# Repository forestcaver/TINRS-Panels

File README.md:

# TINRS-Panels
Tuesday Panel - verified and built

Wobbler Panel - verified and built

Rectangular Thing Panel - verified and built

Hedge Trimmer pcb and panel (Edgecutter with thonkiconn jacks and LP4OA1PBCTG led switch) - verified and built (one hole is not drilled - oops ! I'll update the gerber soon !)

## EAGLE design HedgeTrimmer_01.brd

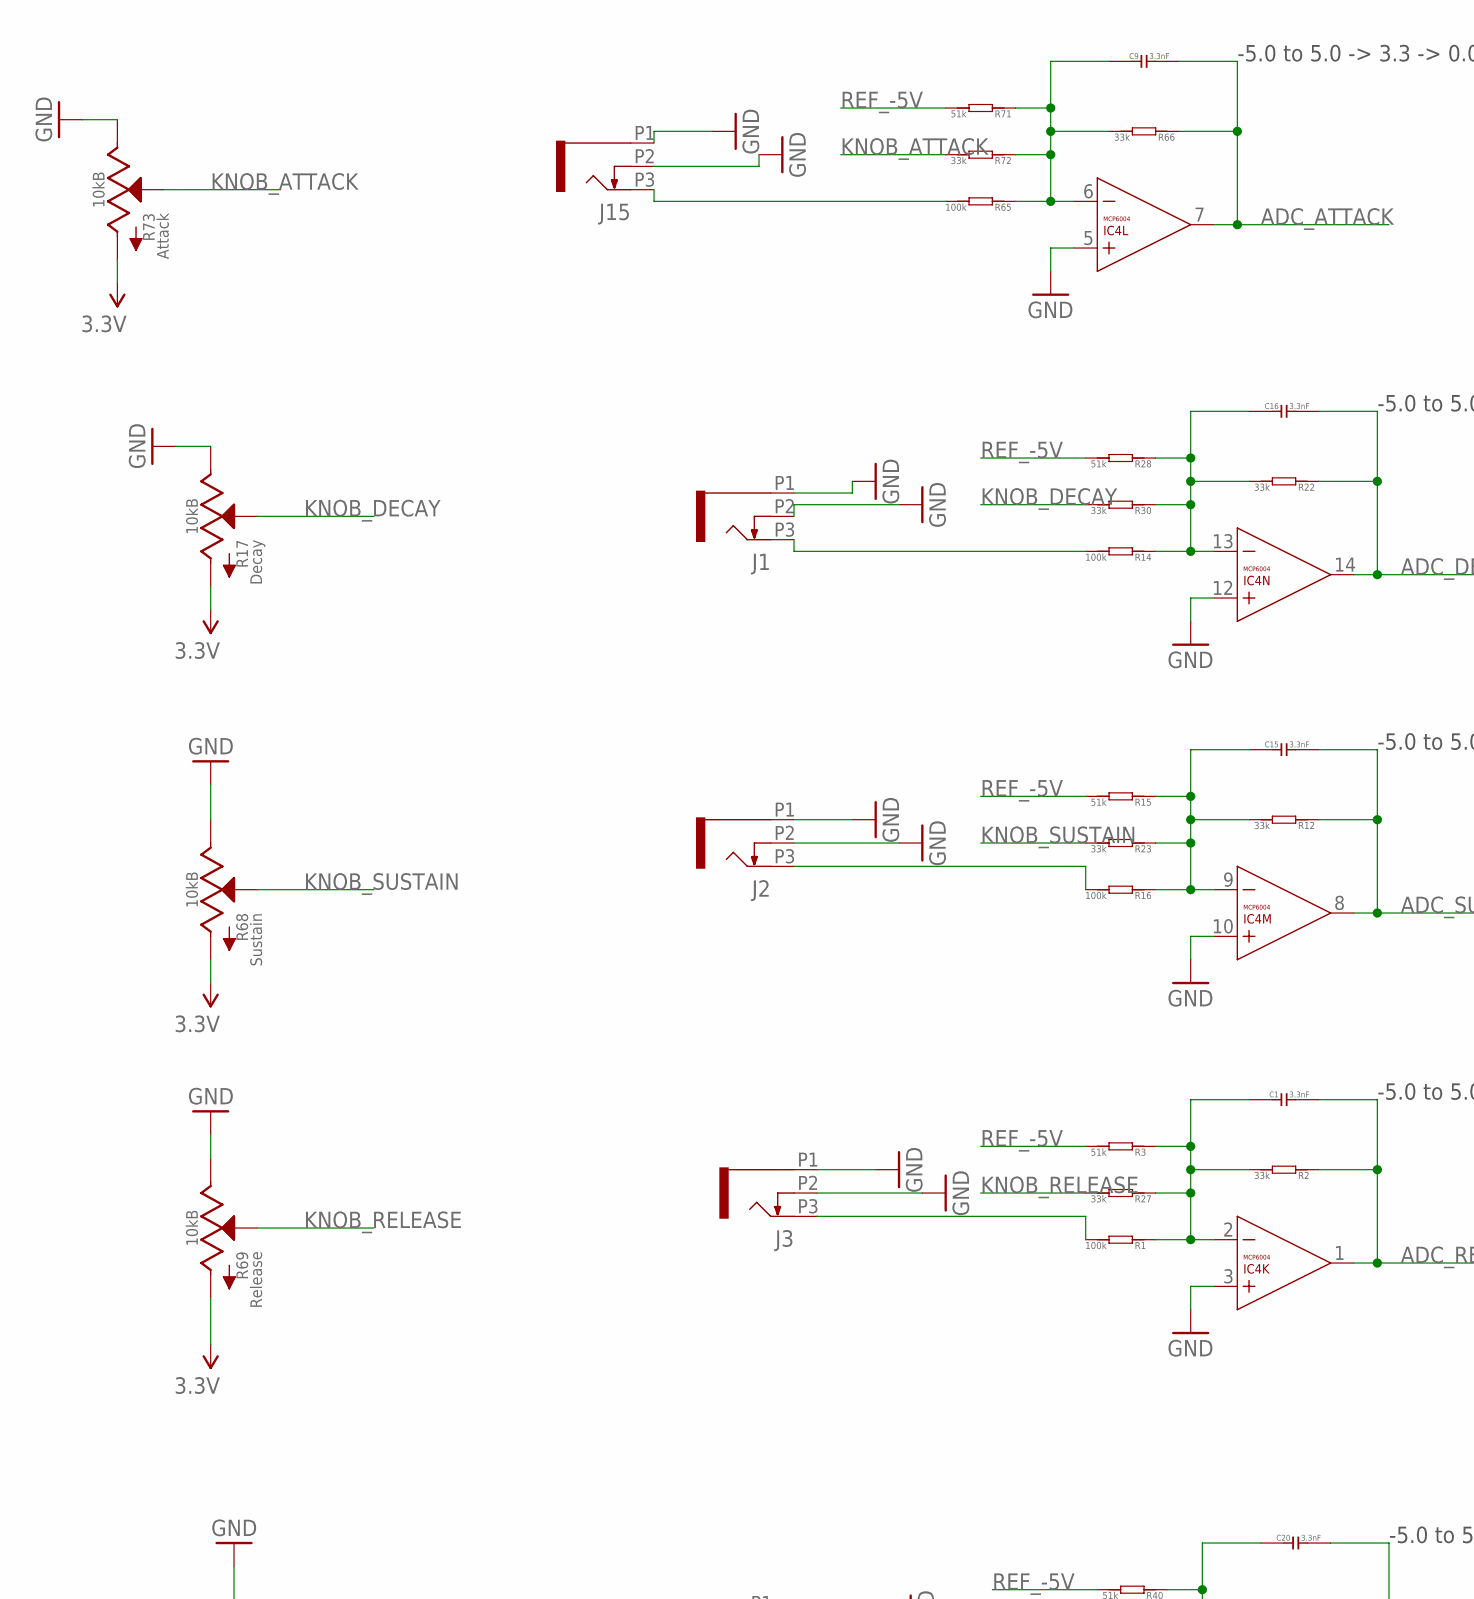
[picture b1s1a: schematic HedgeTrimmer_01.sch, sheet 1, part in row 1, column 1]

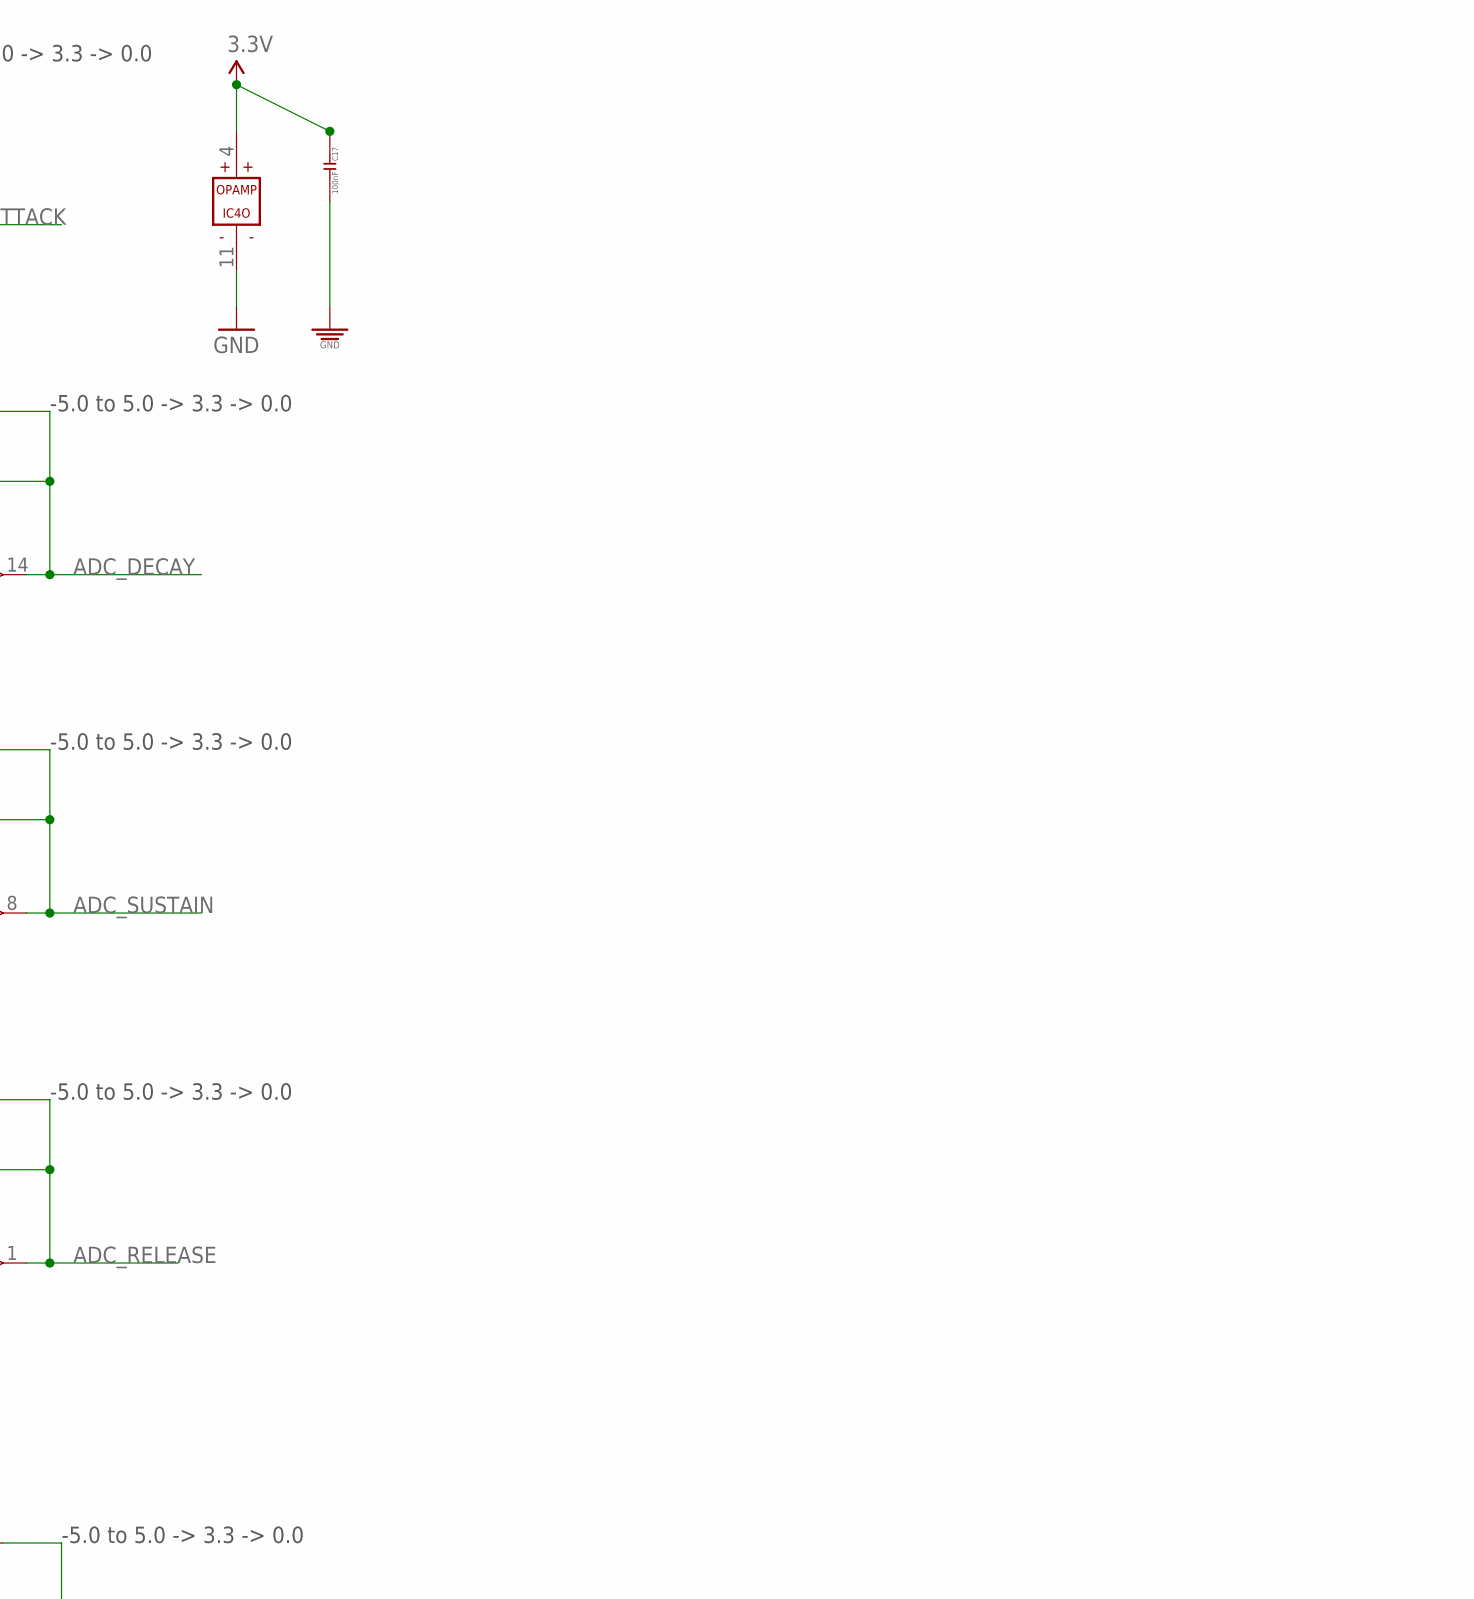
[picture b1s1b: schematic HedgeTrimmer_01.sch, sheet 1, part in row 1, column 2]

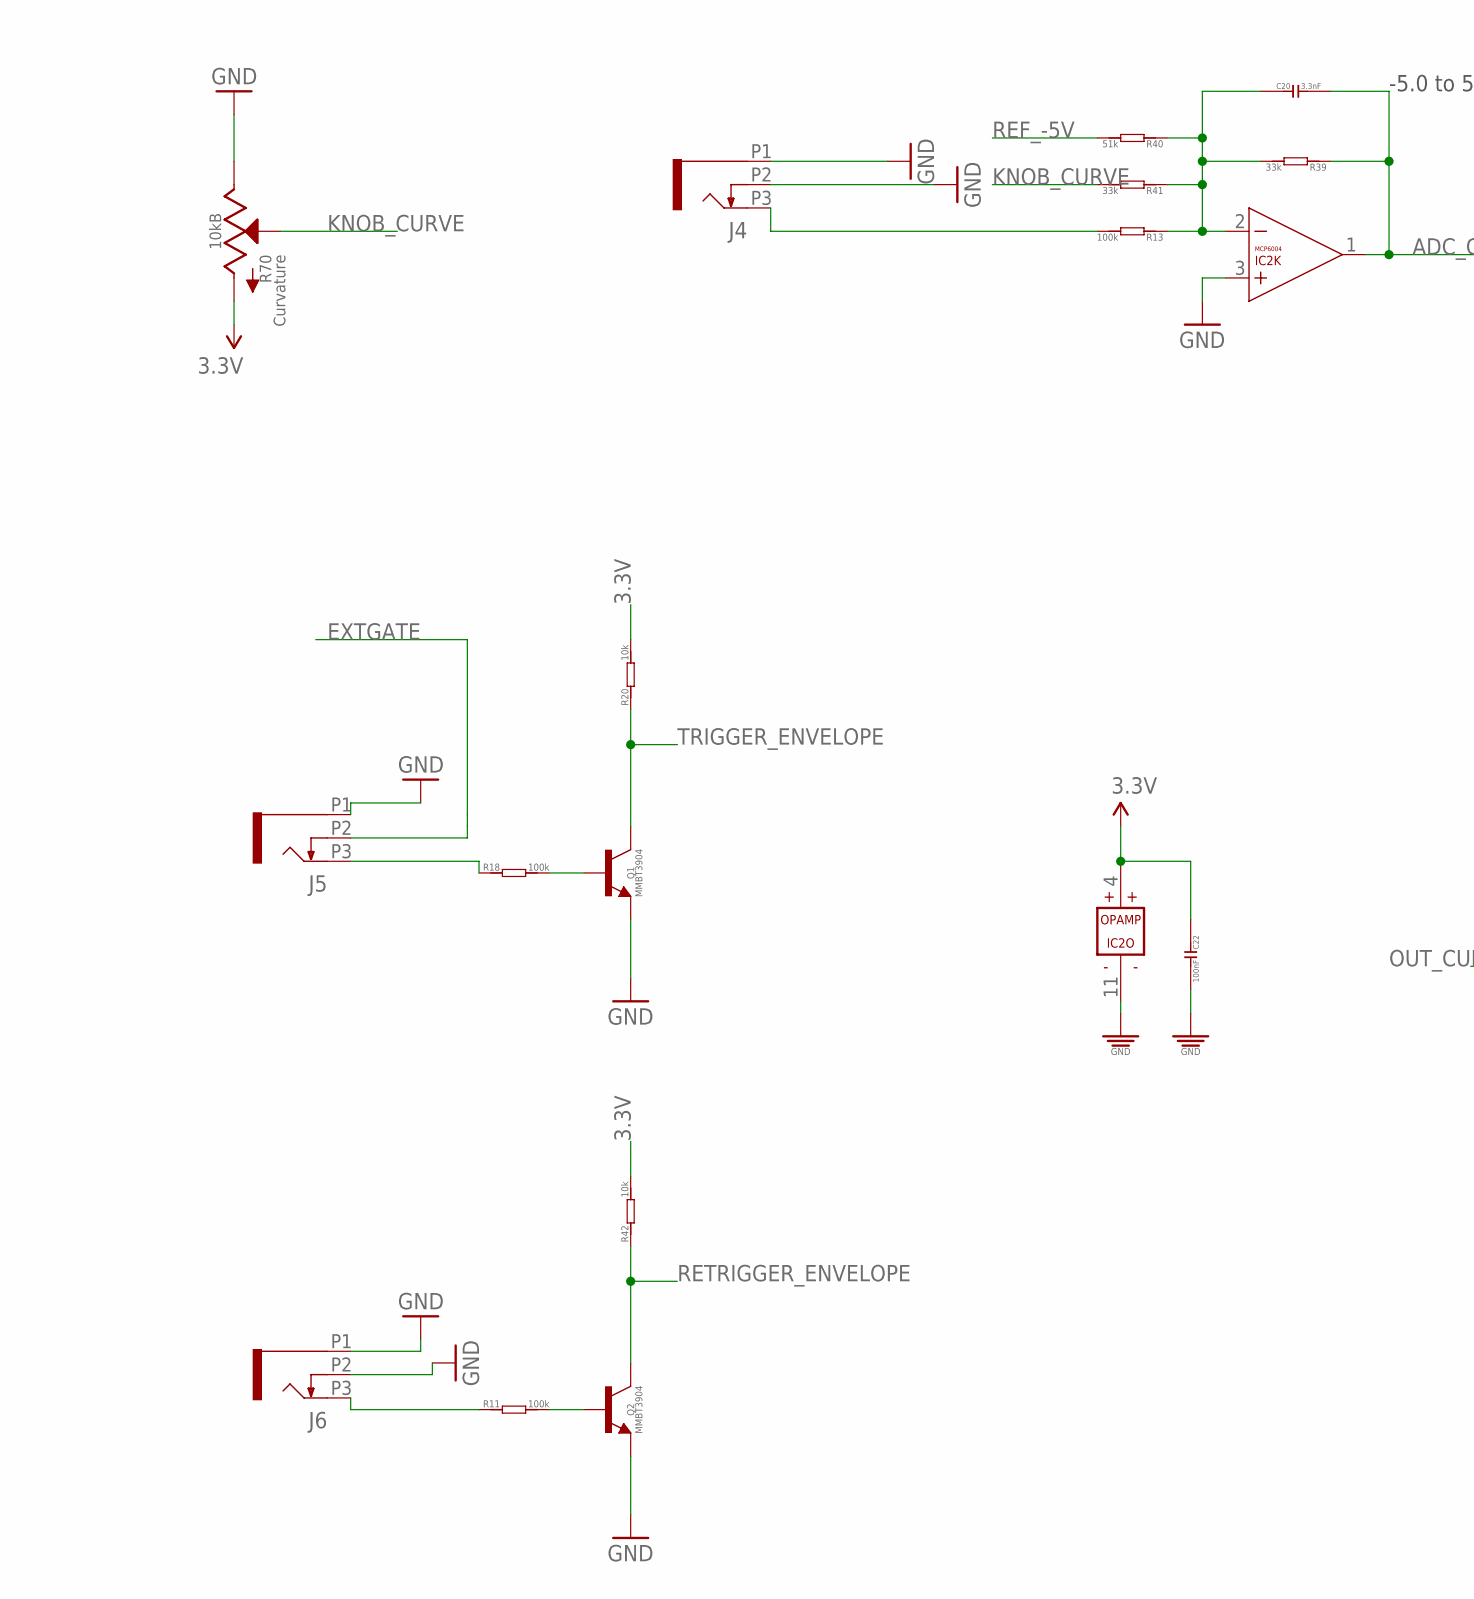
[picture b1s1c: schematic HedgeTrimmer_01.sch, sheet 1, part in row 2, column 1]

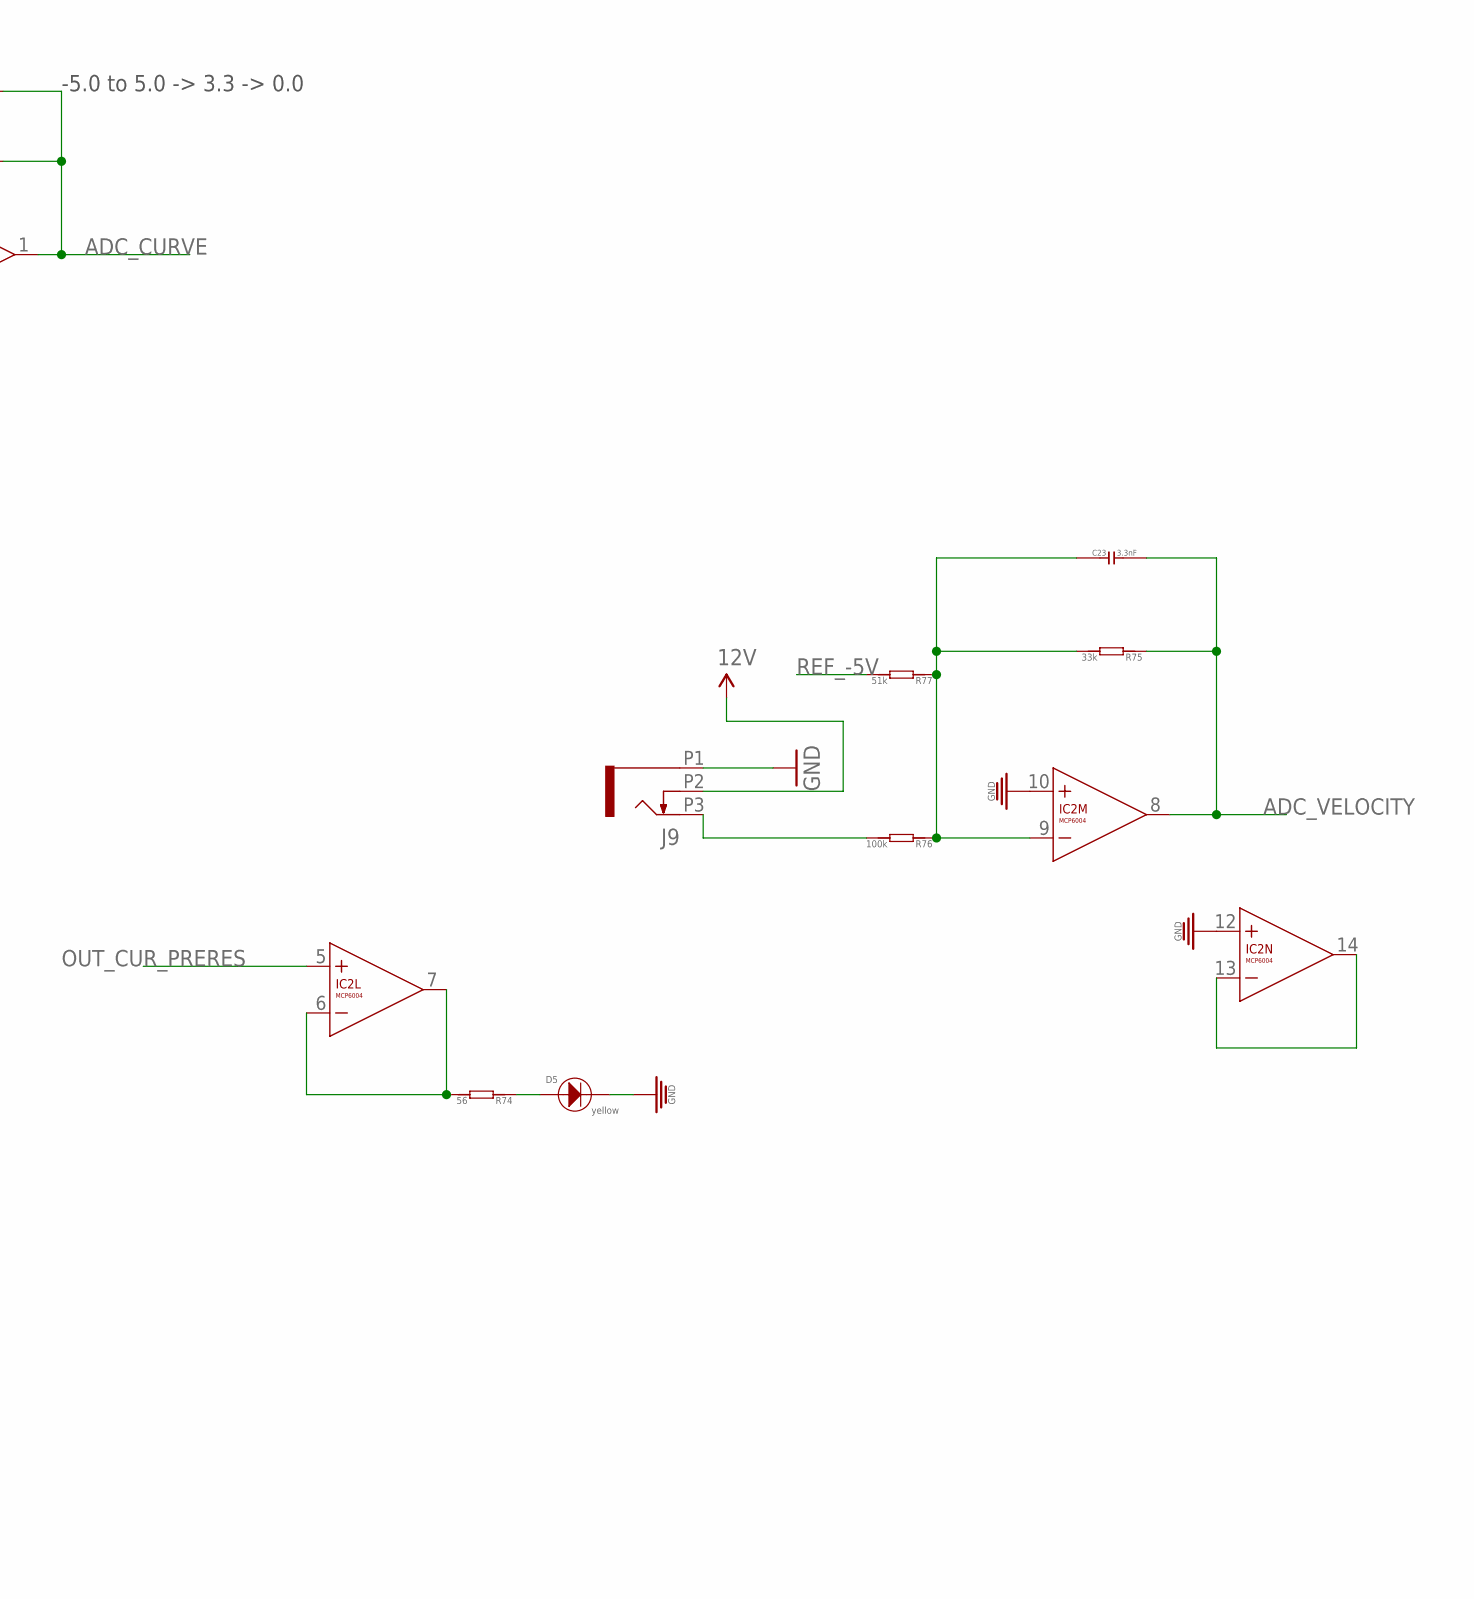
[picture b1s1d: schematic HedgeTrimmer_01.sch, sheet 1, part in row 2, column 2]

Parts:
C1, C9, C15, C16, C20, C23: 3.3nF; C0603
C17, C22: 100nF; C0603; MPN MC0603F104Z160CT
D5: yellow; 3MMLED
IC2, IC4: MCP6004; SO14; MPN MCP6004-I/SL.
J1, J2, J3, J4, J5, J6, J9, J15: PJ301_THONKICONN8; WQP_PJ_301M8
Q1, Q2: MMBT3904; SOT23-BEC; MPN PMBT3904,215
R1, R11, R13, R14, R16, R18, R65, R76: 100k; R0603
R2, R12, R22, R23, R27, R30, R39, R41, R66, R72, R75: 33k; R0603
R3, R15, R28, R40, R71, R77: 51k; R0603
R17, R68, R69, R70, R73: 10kB; OG-POTS_ALPS_POT_VERTICAL
R20, R42: 10k; R0603
R74: 56; R0603

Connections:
3.3V: C17.1, C22.1, IC2.4 (V+), IC4.4 (V+), R17.P$3 (A), R20.2, R42.2, R68.P$3 (A), R69.P$3 (A), R70.P$3 (A), R73.P$3 (A); also elsewhere on the board
12V: J9.P2 (2); also elsewhere on the board
ADC_ATTACK: C9.2, IC4.7 (OUT), R66.1; also elsewhere on the board
ADC_CURVE: C20.2, IC2.1 (OUT), R39.1; also elsewhere on the board
ADC_DECAY: C16.2, IC4.14 (OUT), R22.1; also elsewhere on the board
ADC_RELEASE: C1.2, IC4.1 (OUT), R2.1; also elsewhere on the board
ADC_SUSTAIN: C15.2, IC4.8 (OUT), R12.1; also elsewhere on the board
ADC_VELOCITY: C23.2, IC2.8 (OUT), R75.1; also elsewhere on the board
EXTGATE: J5.P2 (2); also elsewhere on the board
GND: C17.2, C22.2, D5.-, IC2.3 (+IN), IC2.10 (+IN), IC2.11 (V-), IC2.12 (+IN), IC4.3 (+IN), IC4.5 (+IN), IC4.10 (+IN), IC4.11 (V-), IC4.12 (+IN), J1.P1 (1), J1.P2 (2), J2.P1 (1), J2.P2 (2), J3.P1 (1), J3.P2 (2), J4.P1 (1), J4.P2 (2), J5.P1 (1), J6.P1 (1), J6.P2 (2), J9.P1 (1), J15.P1 (1), J15.P2 (2), Q1.E, Q2.E, R17.P$1 (E), R68.P$1 (E), R69.P$1 (E), R70.P$1 (E), R73.P$1 (E); also elsewhere on the board
KNOB_ATTACK: R72.2, R73.P$2 (S)
KNOB_CURVE: R41.2, R70.P$2 (S)
KNOB_DECAY: R17.P$2 (S), R30.2
KNOB_RELEASE: R27.2, R69.P$2 (S)
KNOB_SUSTAIN: R23.2, R68.P$2 (S)
unnamed: J15.P3 (3), R65.2
unnamed: J2.P3 (3), R16.2
unnamed: C15.1, IC4.9 (-IN), R12.2, R15.1, R16.1, R23.1
unnamed: J3.P3 (3), R1.2
unnamed: C1.1, IC4.2 (-IN), R1.1, R2.2, R3.1, R27.1
unnamed: J1.P3 (3), R14.2
unnamed: J4.P3 (3), R13.2
unnamed: Q1.B, R18.2
unnamed: J5.P3 (3), R18.1
unnamed: IC2.6 (-IN), IC2.7 (OUT), R74.2
unnamed: J6.P3 (3), R11.1
unnamed: C9.1, IC4.6 (-IN), R65.1, R66.2, R71.1, R72.1
unnamed: IC2.13 (-IN), IC2.14 (OUT)
unnamed: J9.P3 (3), R76.2
unnamed: C16.1, IC4.13 (-IN), R14.1, R22.2, R28.1, R30.1
unnamed: Q2.B, R11.2
unnamed: C20.1, IC2.2 (-IN), R13.1, R39.2, R40.1, R41.1
unnamed: C23.1, IC2.9 (-IN), R75.2, R76.1, R77.1
unnamed: D5.+, R74.1
OUT_CUR_PRERES: IC2.5 (+IN); also elsewhere on the board
REF_-5V: R3.2, R15.2, R28.2, R40.2, R71.2, R77.2; also elsewhere on the board
RETRIGGER_ENVELOPE: Q2.C, R42.1; also elsewhere on the board
TRIGGER_ENVELOPE: Q1.C, R20.1; also elsewhere on the board

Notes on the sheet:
-5.0 to 5.0 -> 3.3 -> 0.0

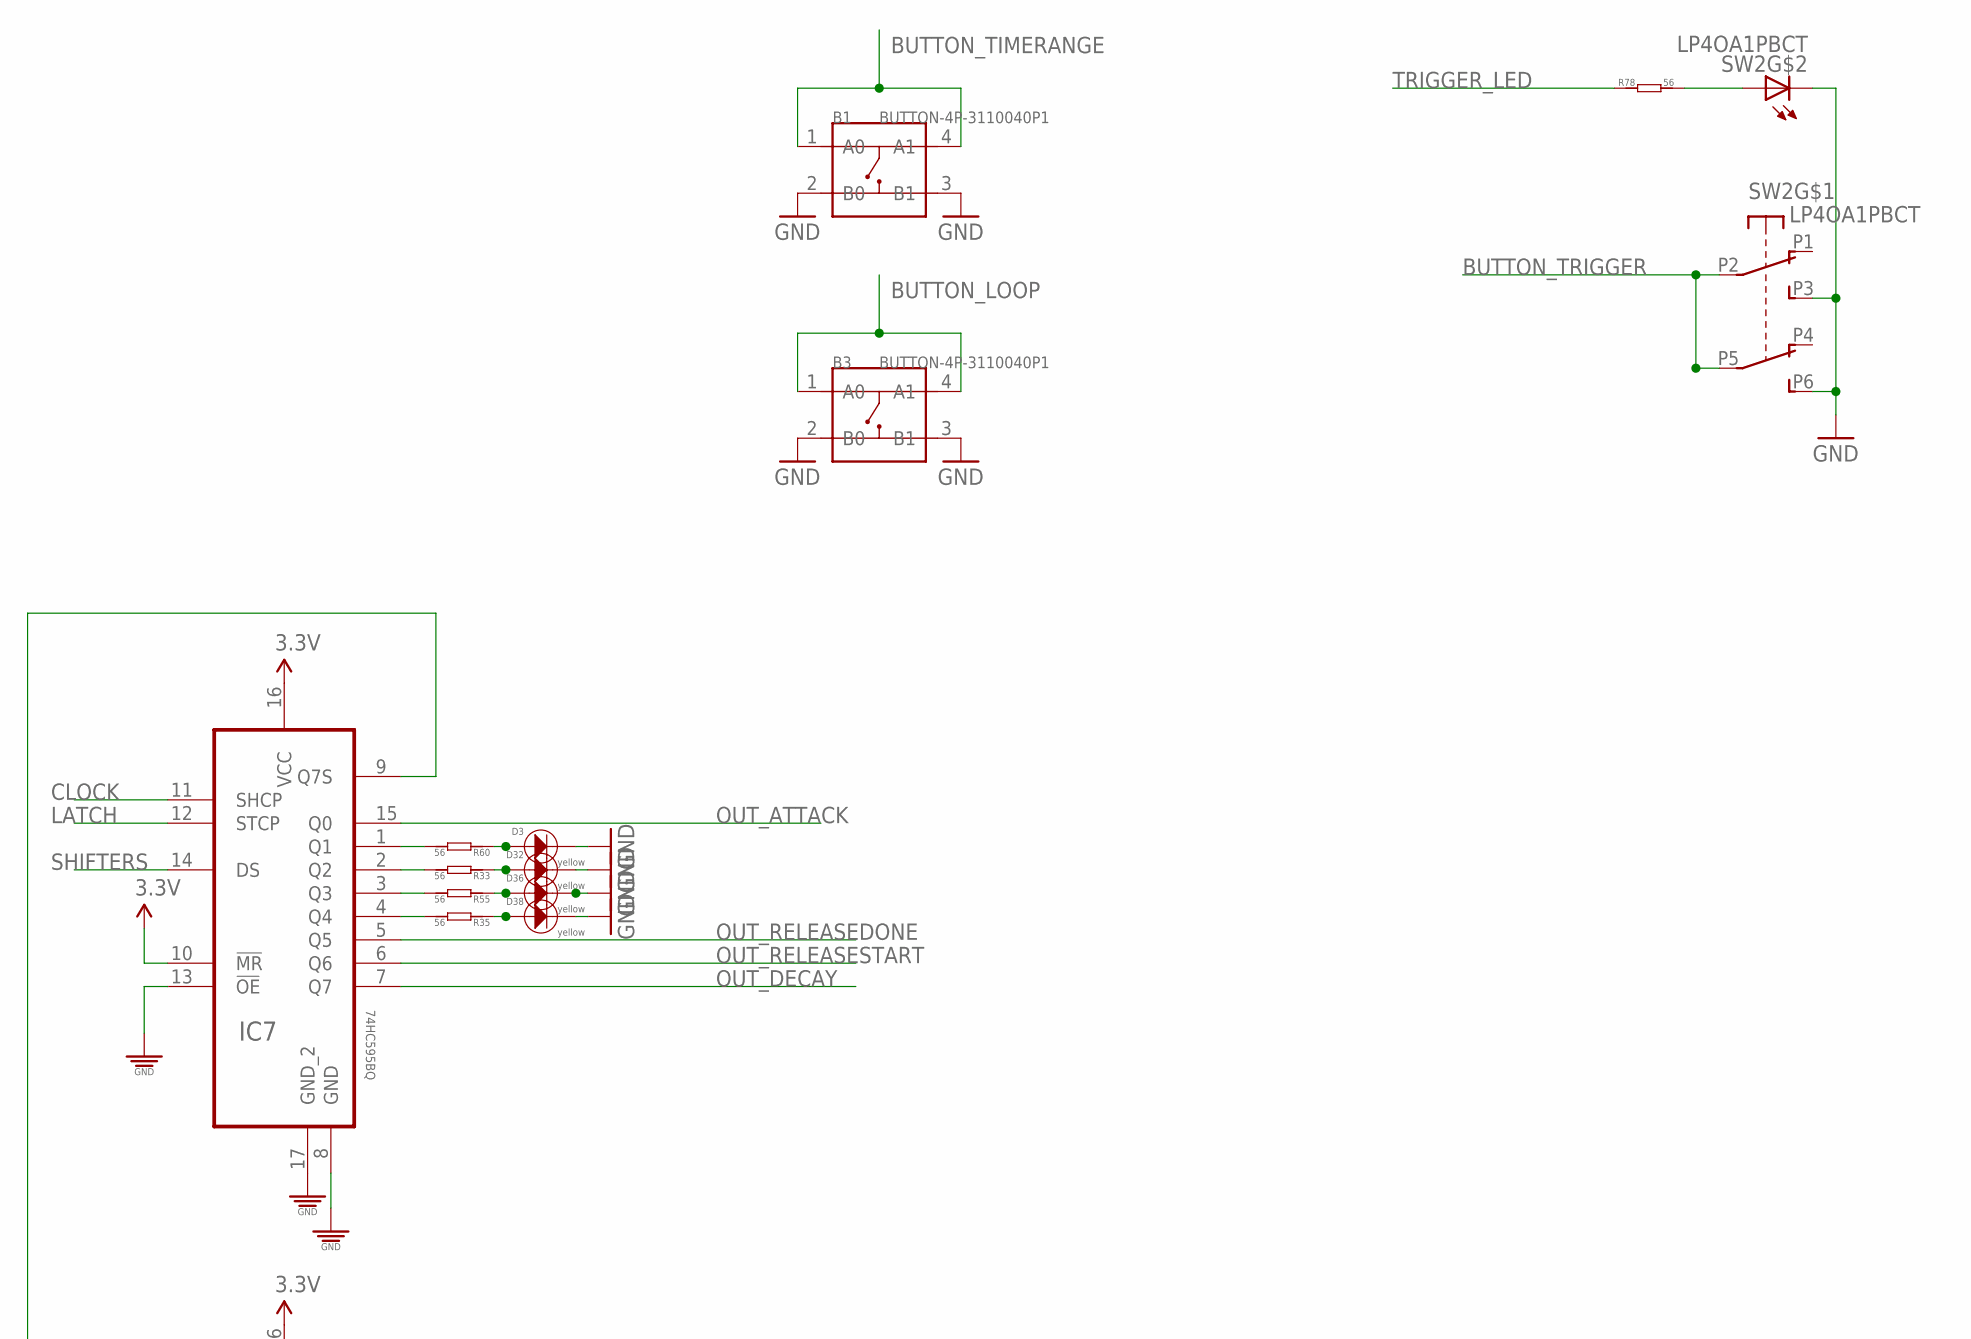
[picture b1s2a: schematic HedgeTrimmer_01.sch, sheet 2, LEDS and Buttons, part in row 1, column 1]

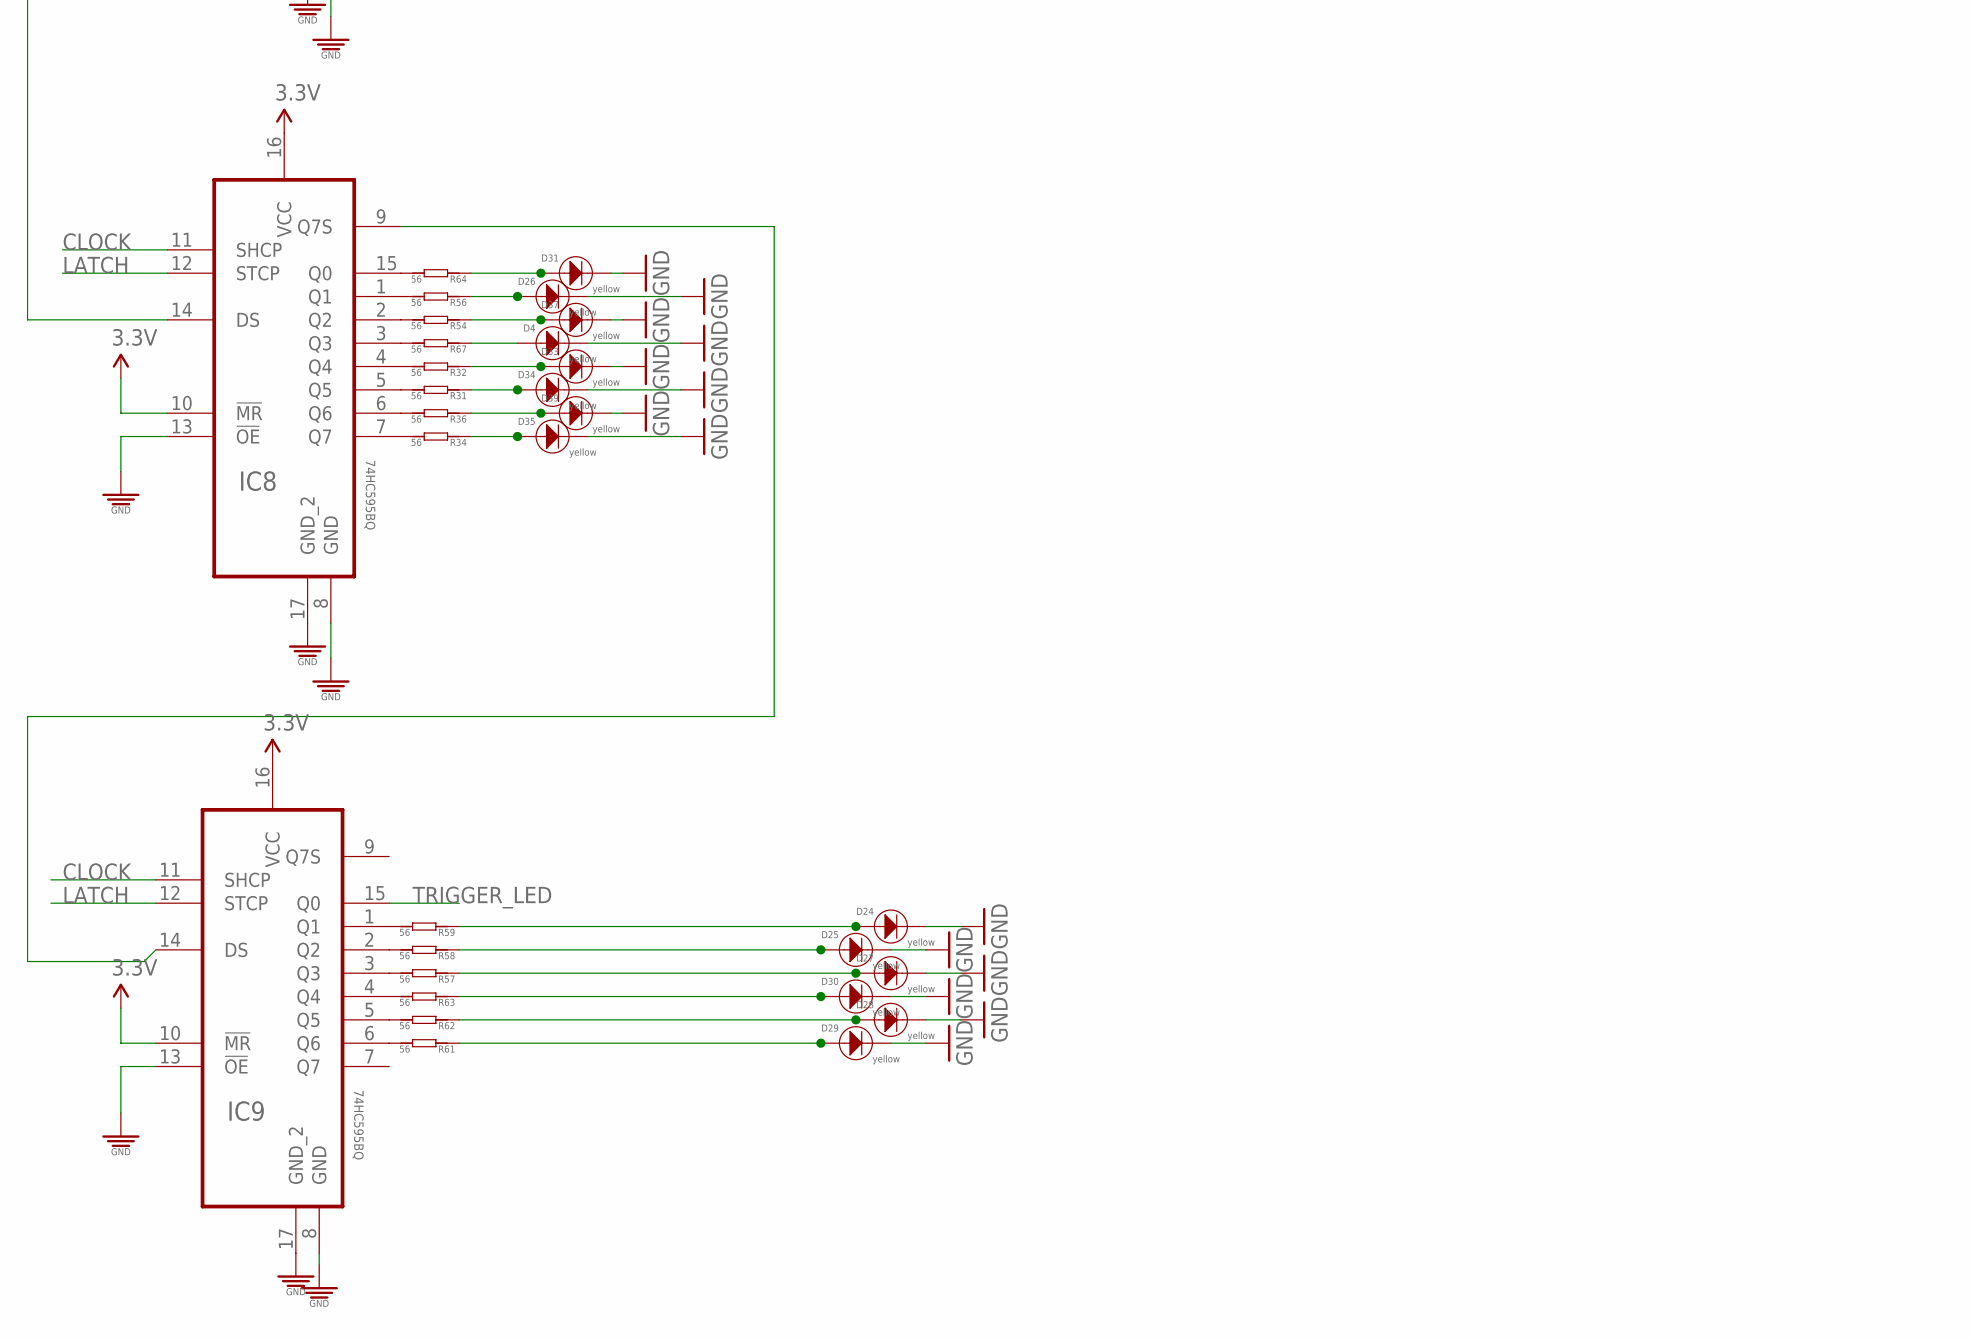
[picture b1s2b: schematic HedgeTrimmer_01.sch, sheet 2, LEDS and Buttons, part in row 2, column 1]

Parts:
B1, B3: BUTTON-4P-3110040P1; 4P-6.0X6.0X5.0H
D3, D4, D24, D25, D26, D27, D28, D29, D30, D31, D32, D33, D34, D35, D36, D37, D38, D39: yellow; 3MMLED
IC7, IC8, IC9: 74HC595BQ; QFN50P250X350X100-17N
R31, R32, R33, R34, R35, R36, R54, R55, R56, R57, R58, R59, R60, R61, R62, R63, R64, R67, R78: 56; R0603
SW2: LP4OA1PBCT

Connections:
3.3V: IC7.10 (!MR), IC7.16 (VCC), IC8.10 (!MR), IC8.16 (VCC), IC9.10 (!MR), IC9.16 (VCC); also elsewhere on the board
BUTTON_LOOP: B3.1 (A0), B3.4 (A1); also elsewhere on the board
BUTTON_TIMERANGE: B1.1 (A0), B1.4 (A1); also elsewhere on the board
BUTTON_TRIGGER: SW2.P2 (A2), SW2.P5 (B2); also elsewhere on the board
CLOCK: IC7.11 (SHCP), IC8.11 (SHCP), IC9.11 (SHCP); also elsewhere on the board
GND: B1.2 (B0), B1.3 (B1), B3.2 (B0), B3.3 (B1), D3.-, D4.-, D24.-, D25.-, D26.-, D27.-, D28.-, D29.-, D30.-, D31.-, D32.-, D33.-, D34.-, D35.-, D36.-, D37.-, D38.-, D39.-, IC7.8 (GND), IC7.13 (!OE), IC7.17 (GND_2), IC8.8 (GND), IC8.13 (!OE), IC8.17 (GND_2), IC9.8 (GND), IC9.13 (!OE), IC9.17 (GND_2), SW2.L2, SW2.P3 (A3), SW2.P6 (B3); also elsewhere on the board
LATCH: IC7.12 (STCP), IC8.12 (STCP), IC9.12 (STCP); also elsewhere on the board
unnamed: R78.2, SW2.L1
unnamed: IC8.7 (Q7), R34.2
unnamed: IC8.15 (Q0), R64.2
unnamed: D28.+, R62.1
unnamed: D4.+, R67.1
unnamed: IC7.1 (Q1), R60.2
unnamed: D29.+, R61.1
unnamed: IC7.2 (Q2), R33.2
unnamed: IC7.3 (Q3), R55.2
unnamed: IC7.4 (Q4), R35.2
unnamed: IC8.1 (Q1), R56.2
unnamed: IC8.2 (Q2), R54.2
unnamed: IC8.3 (Q3), R67.2
unnamed: IC8.4 (Q4), R32.2
unnamed: IC8.5 (Q5), R31.2
unnamed: IC8.6 (Q6), R36.2
unnamed: IC9.1 (Q1), R59.2
unnamed: IC9.2 (Q2), R58.2
unnamed: D3.+, R60.1
unnamed: IC9.3 (Q3), R57.2
unnamed: IC9.4 (Q4), R63.2
unnamed: IC9.5 (Q5), R62.2
unnamed: IC9.6 (Q6), R61.2
unnamed: D27.+, R57.1
unnamed: D26.+, R56.1
unnamed: D25.+, R58.1
unnamed: D24.+, R59.1
unnamed: D30.+, R63.1
unnamed: D31.+, R64.1
unnamed: D32.+, R33.1
unnamed: D33.+, R32.1
unnamed: D34.+, R31.1
unnamed: D35.+, R34.1
unnamed: D36.+, R55.1
unnamed: D37.+, R54.1
unnamed: D38.+, R35.1
unnamed: D39.+, R36.1
OUT_ATTACK: IC7.15 (Q0); also elsewhere on the board
OUT_DECAY: IC7.7 (Q7); also elsewhere on the board
OUT_RELEASEDONE: IC7.5 (Q5); also elsewhere on the board
OUT_RELEASESTART: IC7.6 (Q6); also elsewhere on the board
SHIFTER1TO2: IC7.9 (Q7S), IC8.14 (DS)
SHIFTER2TO3: IC8.9 (Q7S), IC9.14 (DS)
SHIFTERS: IC7.14 (DS); also elsewhere on the board
TRIGGER_LED: IC9.15 (Q0), R78.1

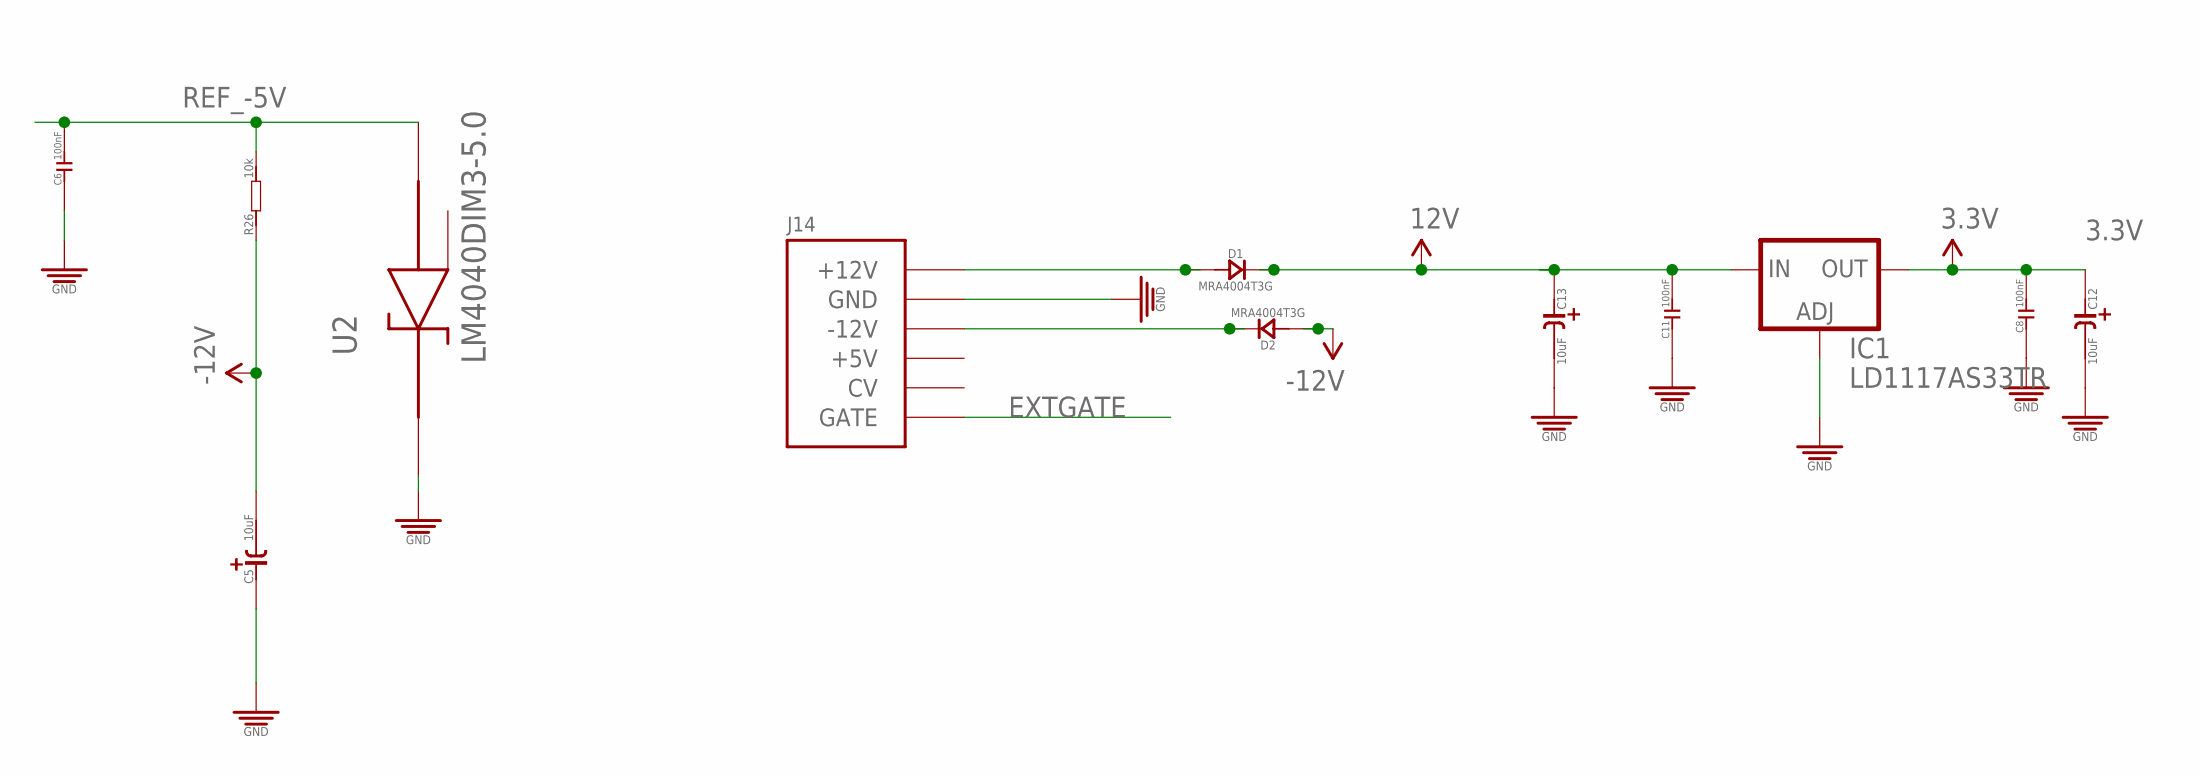
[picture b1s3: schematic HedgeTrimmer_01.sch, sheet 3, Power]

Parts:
C5, C12, C13: 10uF; CASE-A_3216; MPN TAJB106K020RNJ
C6: 100nF; C0603; MPN 06035C104KAT2A
C8, C11: 100nF; C0603; MPN MC0603F104Z160CT
D1, D2: MRA4004T3G; DO-214AC; MPN US1G-E3/5AT
IC1: LD1117AS33TR; SOT223; MPN LD1117AS33TR
J14: POWERSMT; 2X08_SMT_HEADER
R26: 10k; R0603
U2: LM4040DIM3-5.0; SOT95P237X112-3N

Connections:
3.3V: C8.2, C12.+ (1), IC1.2 (OUT), IC1.4 (OUT); also elsewhere on the board
12V: C11.2, C13.+ (1), D1.2 (-), IC1.3 (IN); also elsewhere on the board
-12V: C5.- (2), D2.1 (+), R26.1; also elsewhere on the board
EXTGATE: J14.15 (GATE), J14.16 (GATE); also elsewhere on the board
GND: C5.+ (1), C6.1, C8.1, C11.1, C12.- (2), C13.- (2), IC1.1 (ADJ), J14.3 (GND), J14.4 (GND), J14.5 (GND), J14.6 (GND), J14.7 (GND), J14.8 (GND), U2.1 (CATHODE); also elsewhere on the board
unnamed: D1.1 (+), J14.9 (+12V), J14.10 (+12V)
unnamed: D2.2 (-), J14.1 (-12V), J14.2 (-12V)
REF_-5V: C6.2, R26.2, U2.2 (ANODE); also elsewhere on the board

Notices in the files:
parts and their libraries:
SparkFun-Aesthetics: Licensing: CC v3.0 Share-Alike You are welcome to use this library for commercial purposes.
